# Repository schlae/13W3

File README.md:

# 13W3 Video Snake Oil

Do you have an old workstation with a 13W3-style video connector? Are you frustrated with adapters that claim to convert this to a 15-pin analog VGA, but don't seem to work? Then this project is for you.

[Schematic](https://github.com/schlae/13W3/blob/main/13W3.pdf)

[Fab files](https://github.com/schlae/13W3/blob/main/fab/13W3_Rev1.zip)

Board dimensions: 52mm x 53.6mm. 2-layers, standard board thickness. Fabricate it using whatever soldermask and silkscreen colors you prefer.

## Assembly

Unless you need the composite sync separator, assembly is easy: just install J1 (a 13W3 connector, Mouser 636-685M13W3103L461 or equivalent) and J2 (a high-density 15-pin D shell connector, Mouser 636-181-015-213R561 or equivalent). Be warned that the 13W3 connector is quite expensive, so you may want to look at online auction sites or surplus sources.

You will need to solder some jumper wires to configure the 13W3 adapter for the particular workstation you are using. Ground pads are located next to the pads that are marked with the pin number that they are connected to. Using the table below, connect the pads to ground, leave them floating, or jumper them to the H (horizontal sync) or V (vertical sync) pads.

| 13W3 pin | Sun (old)          | Sun (DDC)        | RS/6000 [1]     | SGI (old) [2]    | SGI (DDC) [2]   |
|----------|--------------------|------------------|-----------------|------------------|-----------------|
| 1        | n/c (serial read)  | n/c (DDC SCL)    | Gnd (ID-2)      | n/c (id3)        | n/c (DDC SCL)   |
| 2        | n/c (Vsync) [3]    | n/c (DDC 5V in)  | n/c (ID-3)      | n/c (id0)        | n/c (DDC SDA)   |
| 3        | n/c (sense2) [6]   | n/c (sense2) [6] | Gnd (self test) | n/c (Csync)  [5] | n/c (Csync)     |
| 4        | Gnd (for sense)    | Gnd (for DDC)    | Gnd             | n/c (Hdrive) [5] | H               |
| 5        | H (Csync) [3]      | H (Csync) [4]    | H               | n/c (Vdrive) [5] | V               |
| 6        | n/c (Hsync) [3]    | n/c (DDC SDA)    | Gnd (ID-0)      | n/c (id1)        | n/c (DDC 5V in) |
| 7        | n/c (serial write) | n/c (Vsync) [4]  | n/c (ID-1)      | n/c (id2)        | Gnd (for DDC)   |
| 8        | n/c (sense1) [6]   | n/c (sense1) [6] | n/c             | Gnd              | Gnd             |
| 9        | n/c (sense0) [6]   | n/c (sense0) [6] | V               | Gnd              | Gnd             |
| 10       | Gnd (for sync)     | Gnd (for sync)   | Gnd             | Gnd              | Gnd             |

Notes:
1. The RS/6000 is wired for monitor ID 1010.
2. The SGI wiring connections have not been tested but should work.
3. Some video cards with Sun's old pinout lack Hsync and Vsync, so we connect Csync to the H pad, but see [§ Composite Sync](#composite-sync-and-sync-on-green) for more details.
4. All video cards with Sun's DDC pinout lack Hsync, so we connect Csync to the H pad, but see [§ Composite Sync](#composite-sync-and-sync-on-green) for more details.
5. Hdrive and Vdrive are not equivalent to Hsync and Vsync, so we connect Csync to the H pad, but see [§ Composite Sync](#composite-sync-and-sync-on-green) for more details.
6. Sense codes control the default resolution and refresh rate, unless DDC is supported and connected to your VGA monitor.
    * default sense code 000<sub>2</sub> is 1152x900@66
    * jump pins 3 and 9 to Gnd (101<sub>2</sub>) for 1280x1024@76
    * jump pin 8 to Gnd (010<sub>2</sub>) for 1024x768@60
    * for other sense codes, see [TurboGX/TurboGXplus Hardware Installation Guide](https://docs.oracle.com/cd/E19957-01/801-5399-10/801-5399-10.pdf), Table C-3
    * not all sense codes are supported by all video cards, see the Sun [Frame Buffer FAQ](http://www.sunhelp.org/faq/FrameBuffer.html#5)

Once you finish the wiring, it's a good idea to mark the board with the name of the system it is wired for. The space underneath the silkscreen text "FOR BEST RESULTS USE WITH:" is provided for this purpose.

If you figure out the wiring for a system not in this table, feel free to file a bug report or submit a pull request.

### Composite Sync and Sync-On-Green

Some workstations output composite sync (Csync) or sync-on-green but not separate sync (Hsync and Vsync), such as the SPARCstation 5 with TurboGX.

Many modern LCD monitors already support one or both of these. In the case of sync-on-green, you may not need to wire up any sync signals at all, whereas for composite sync, it may be enough to connect your Csync pin to the H pad.

If yours doesn't support those, then you'll need to install these components:

| Q | Designator | Description | Mouser part number |
|---|------------|-------------|--------------------|
| 2 | C1, C3     | 0.1uF X5R 50V capacitor, 0603 | |
| 1 | C2 | 560pF C0G 50V capacitor, 0603 | |
| 1 | R1 | 100 ohm 5% 0603 resistor | |
| 1 | R2 | 10.0K ohm 1% 0603 resistor | |
| 1 | U1 | LMH1980 sync separator | 926-LMH1980MM/NOPB |

To separate sync-on-green, install a jumper wire across JP11. For composite sync, run a wire from the JP11 pad nearest R1 (marked CSYNC) to the appropriate pin on the 13W3 connector. Be sure to disconnect your Csync pin from the H pad, if you connected it earlier.

For this circuit to work, it needs 5V power, provided by J5 on the PCB (marked "5V GND"). If your workstation does not provide 5V on the 13W3 connector, you'll need to get it from somewhere else (keyboard port, external DC power supply, etc).

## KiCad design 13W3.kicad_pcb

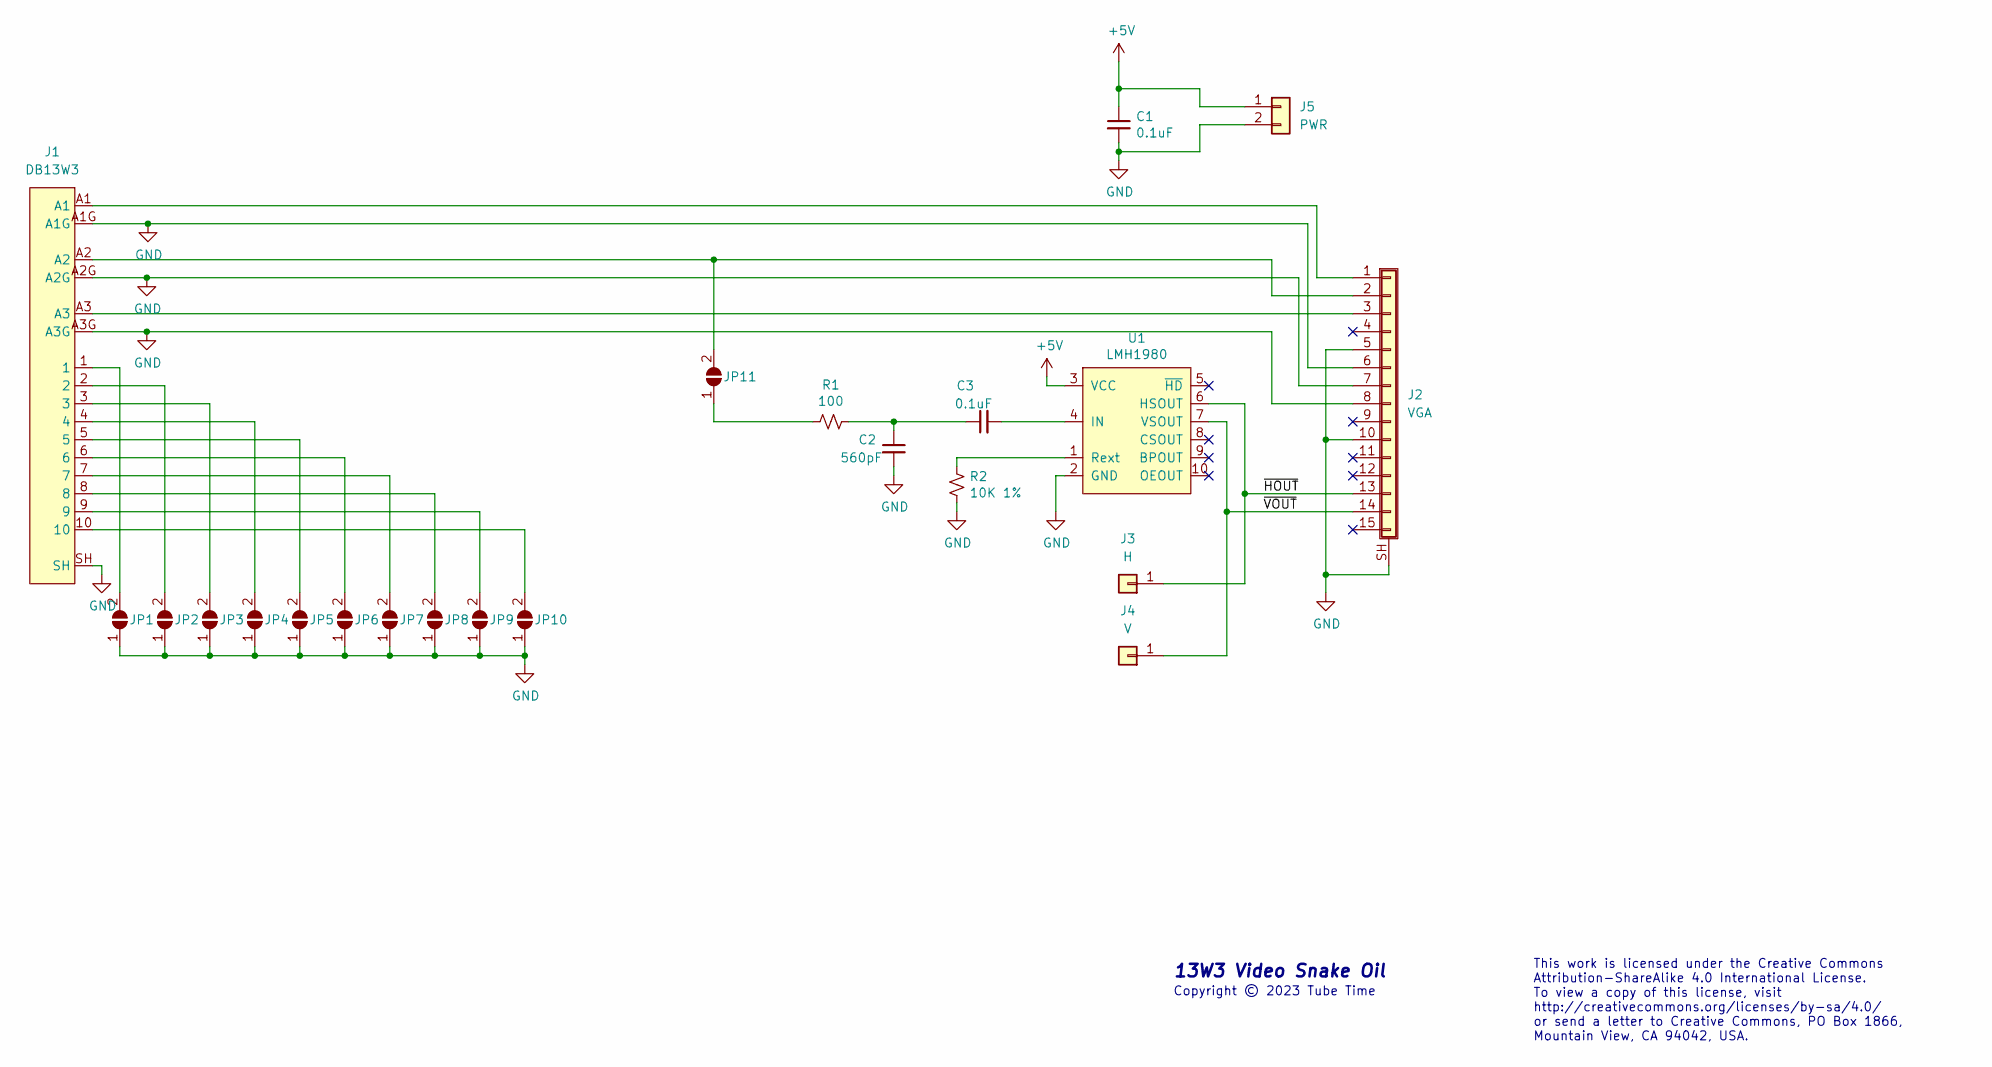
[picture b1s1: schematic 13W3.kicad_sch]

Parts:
C1, C3: 0.1uF; CAPC2012X55
C2: 560pF; CAPC2012X55
J1: DB13W3; DSUB-13W3; Mouser 636-685M13W3103L461
J2: VGA; DB15HDFC; Mouser 636-181-015-213R561
J3: H; TestPoint_Pad_1.0x1.0mm
J4: V; TestPoint_Pad_1.0x1.0mm
J5: PWR; PinHeader_1x02_P2.54mm_Vertical
JP1, JP2, JP3, JP4, JP5, JP6, JP7, JP8, JP9, JP10, JP11: SolderJumper_2_Open; RESC2012X55
R1: 100; RESC2012X55
R2: 10K 1%; RESC2012X55
U1: LMH1980; SSOP50P500X110-10

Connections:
+5V: C1.1, J5.1, U1.3 (VCC)
/~HOUT: J2.13, J3.1, U1.6 (HSOUT)
/~VOUT: J2.14, J4.1, U1.7 (VSOUT)
GND: C1.2, C2.2, J1.A1G, J1.A2G, J1.A3G, J1.SH, J2.5, J2.6, J2.7, J2.8, J2.10, J2.SH (Shield), J5.2, JP1.1 (A), JP2.1 (A), JP3.1 (A), JP4.1 (A), JP5.1 (A), JP6.1 (A), JP7.1 (A), JP8.1 (A), JP9.1 (A), JP10.1 (A), R2.1, U1.2 (GND)
unnamed: C2.1, C3.1, R1.1
unnamed: J1.1, JP1.2 (B)
unnamed: J1.2, JP2.2 (B)
unnamed: J1.3, JP3.2 (B)
unnamed: J1.4, JP4.2 (B)
unnamed: J1.5, JP5.2 (B)
unnamed: J1.6, JP6.2 (B)
unnamed: J1.7, JP7.2 (B)
unnamed: J1.8, JP8.2 (B)
unnamed: J1.9, JP9.2 (B)
unnamed: J1.10, JP10.2 (B)
unnamed: J1.A1, J2.1
unnamed: J1.A2, J2.2, JP11.2 (B)
unnamed: J1.A3, J2.3
unnamed: JP11.1 (A), R1.2
unnamed: R2.2, U1.1 (Rext)
unnamed: C3.2, U1.4 (IN)

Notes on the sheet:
This work is licensed under the Creative Commons Attribution-ShareAlike 4.0 International License. To view a copy of this license, visit http://creativecommons.org/licenses/by-sa/4.0/ or send a letter to Creative Commons, PO Box 1866, Mountain View, CA 94042, USA.
Copyright © 2023 Tube Time
13W3 Video Snake Oil

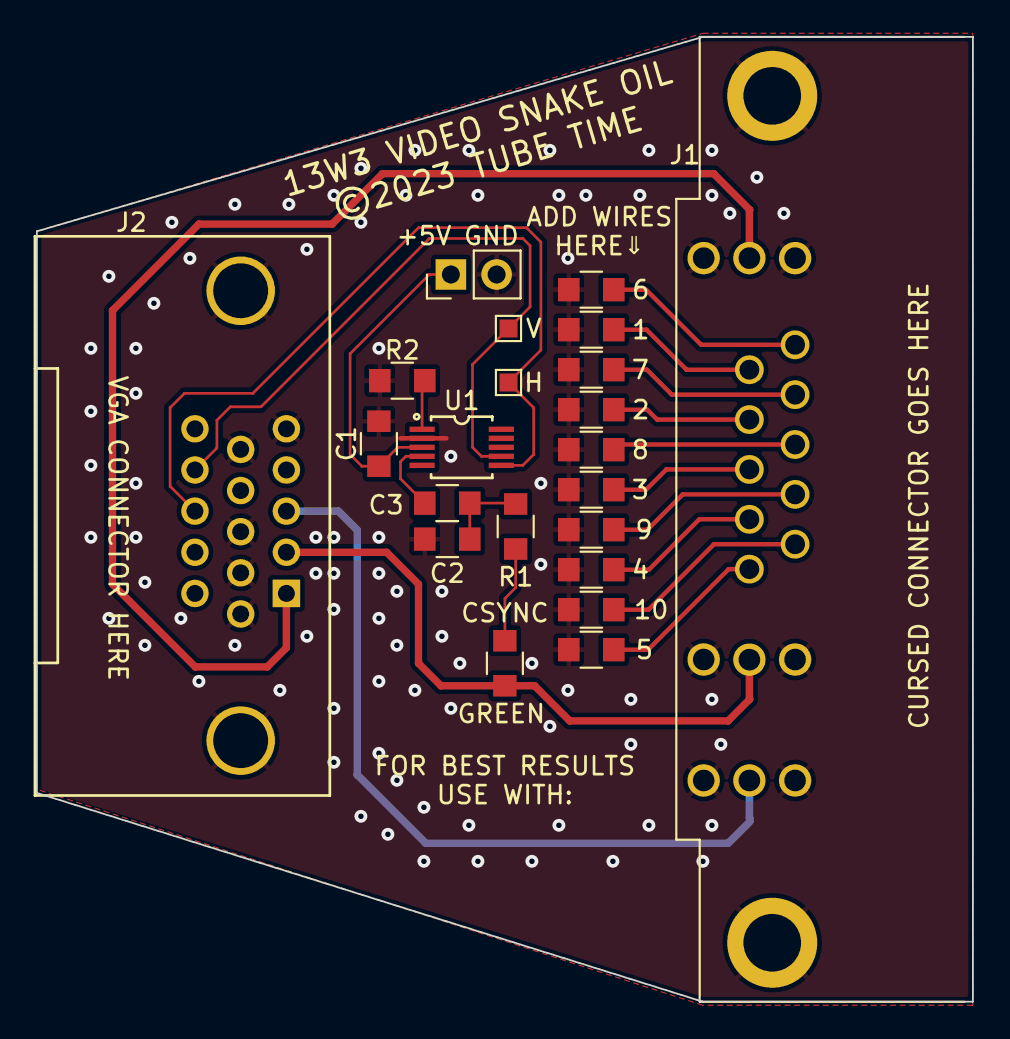
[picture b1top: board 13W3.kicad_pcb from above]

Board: 2 copper layers, 52.0 x 53.6 mm, 22 parts (0 on the bottom side), 21 nets.

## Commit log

2023-07-16 Added photo
2023-09-30 Improve docs for Sun workstations and composite sync
2023-09-30 Add note about Sun sense code compatibility
2023-09-30 Add column for SGI’s newer DDC pinout; fix SGI’s old pinout
2023-09-30 Linkify each “§ Composite Section”

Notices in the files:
13W3.kicad_pcb:
Copyright (C) 2023 Tube Time
